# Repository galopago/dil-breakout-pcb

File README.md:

# BREAKOUT BOARDS FOR RF MODULES

Open source breakout boards for "stamp like" rf modules. Good for experimenting on a breadboard or to be used as sub-boards.

Read this in other languages: [Español](/assets/markdown/README.es.md)

Main features:

* Every pin is accessible
* Compatible with solderless breadboard
* Double row header for maximizing free space on prototype boards

Breadboard                              | Space saver right angle                    | Space saver rised                           
----------------------------------------|--------------------------------------------|---------------------------------------------
 |  | 

## Versions

There are several board versions, each one with different personalities

| HINT     | CHIP                  | LINK                                     
|----------|-----------------------|--------------------------------------
| RAK3172  | STM32WLE5CC           | [RAK3172](/rak3172)  
| RAK11300 | RP2040+SX1262         | [RAK11300](/rak11300)  
| SA818    | RENESAS MCU ?+RDA1846 | [SA818](/sa818)
| MS88SF2  | nRF52840              | [MS88SF2](/ms88sf2)

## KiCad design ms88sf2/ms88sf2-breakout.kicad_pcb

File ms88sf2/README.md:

# BREAKOUT BOARD FOR MS88SF2 MODULE

This board allows [Minew MS88SF2 modules](assets/pdf/MS88SF2elp
e.pdf) to be used on breadboard for prototyping. Open source and manufacturing files available. The main features are:

* Every pin is accessible
* Compatible with solderless breadboard
* Double row header for maximizing free space on prototype boards

## How to use this repository

The PCB was developed in KiCad V5.1,

## Directory structure

* The root folder contains template KiCad files: project, schematic and PCB 
* /library folder contains additional symbols needed to edit printed schematic
* /modules folder contains additional footprints needed to edit printed circuit board
* /gerber folder contains ready to manufacture files.
* /assets folder contains support files for reade.md

## PINOUT

## BREADBOARD

Pitch compatible with solderless breadboard

## DOUBLE ROW RIGHT ANGLE

Space saver option when enclosure's height allows it

 FRONT                             | SIDE                             | UPPER                            
-----------------------------------|----------------------------------|-----------------------------------
||

## DOUBLE ROW RISED

Space saver option for batteries or additional electronics. Uses long pin headers with spacers to reach the maximun allowable height

 SIDE                              | RISED                          
-----------------------------------|--------------------------------
|

## PCB

 SINGLE                            | PANEL                          
-----------------------------------|--------------------------------
|

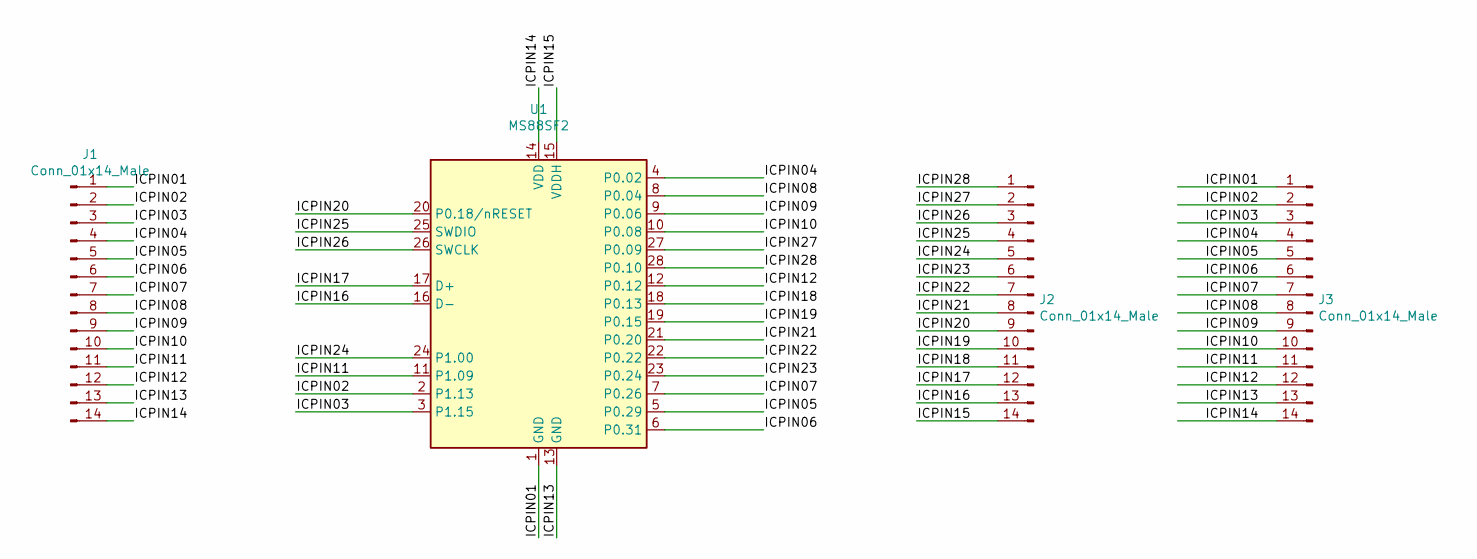
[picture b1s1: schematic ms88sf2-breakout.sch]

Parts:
J1, J2, J3: Conn_01x14_Male; PinHeader_1x14_P2.54mm_Vertical
U1: MS88SF2

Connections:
/ICPIN01: J1.1, J3.1, U1.1 (GND)
/ICPIN02: J1.2, J3.2, U1.2 (P1.13)
/ICPIN03: J1.3, J3.3, U1.3 (P1.15)
/ICPIN04: J1.4, J3.4, U1.4 (P0.02)
/ICPIN05: J1.5, J3.5, U1.5 (P0.29)
/ICPIN06: J1.6, J3.6, U1.6 (P0.31)
/ICPIN07: J1.7, J3.7, U1.7 (P0.26)
/ICPIN08: J1.8, J3.8, U1.8 (P0.04)
/ICPIN09: J1.9, J3.9, U1.9 (P0.06)
/ICPIN10: J1.10, J3.10, U1.10 (P0.08)
/ICPIN11: J1.11, J3.11, U1.11 (P1.09)
/ICPIN12: J1.12, J3.12, U1.12 (P0.12)
/ICPIN13: J1.13, J3.13, U1.13 (GND)
/ICPIN14: J1.14, J3.14, U1.14 (VDD)
/ICPIN15: J2.14, U1.15 (VDDH)
/ICPIN16: J2.13, U1.16 (D-)
/ICPIN17: J2.12, U1.17 (D+)
/ICPIN18: J2.11, U1.18 (P0.13)
/ICPIN19: J2.10, U1.19 (P0.15)
/ICPIN20: J2.9, U1.20 (P0.18/nRESET)
/ICPIN21: J2.8, U1.21 (P0.20)
/ICPIN22: J2.7, U1.22 (P0.22)
/ICPIN23: J2.6, U1.23 (P0.24)
/ICPIN24: J2.5, U1.24 (P1.00)
/ICPIN25: J2.4, U1.25 (SWDIO)
/ICPIN26: J2.3, U1.26 (SWCLK)
/ICPIN27: J2.2, U1.27 (P0.09)
/ICPIN28: J2.1, U1.28 (P0.10)

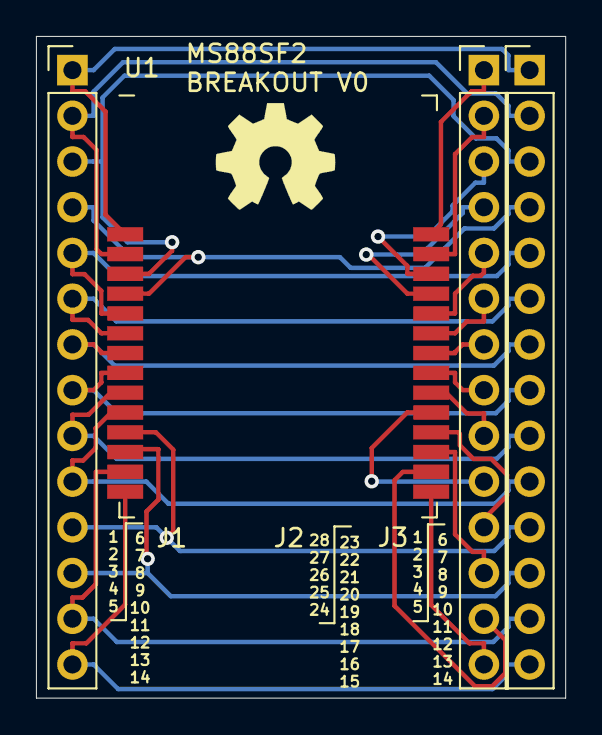
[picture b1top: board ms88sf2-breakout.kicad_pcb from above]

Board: 2 copper layers, 29.4 x 36.8 mm, 4 parts (0 on the bottom side), 28 nets.

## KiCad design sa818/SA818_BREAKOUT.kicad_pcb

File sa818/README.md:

# BREAKOUT BOARD FOR SA818 MODULE

This board allows [NiceRF SA818 modules](assets/pdf/SA818.pdf) to be used on breadboard for prototyping. Open source and manufacturing files available. The main features are:

* Every pin is accessible
* Compatible with solderless breadboard
* Double row header for maximizing free space on prototype boards
* Pads for U.Fl RF connector
* Pads for custom output pi filter

## How to use this repository

The PCB was developed in KiCad V5.1,

## Directory structure

* The root folder contains template KiCad files: project, schematic and PCB 
* /library folder contains additional symbols needed to edit printed schematic
* /modules folder contains additional footprints needed to edit printed circuit board
* /gerber folder contains ready to manufacture files.
* /assets folder contains support files for reade.md

## PINOUT

## BREADBOARD

Pitch compatible with solderless breadboard

## DOUBLE ROW RIGHT ANGLE

Space saver option when enclosure's height allows it

 FRONT                             | SIDE                             | UPPER                            
-----------------------------------|----------------------------------|-----------------------------------
||

## DOUBLE ROW RISED

Space saver option for batteries or additional electronics. Uses long pin headers with spacers to reach the maximun allowable height

 SIDE                              | RISED                          
-----------------------------------|--------------------------------
|

## PCB

 SINGLE                            | PANEL                          
-----------------------------------|--------------------------------
|

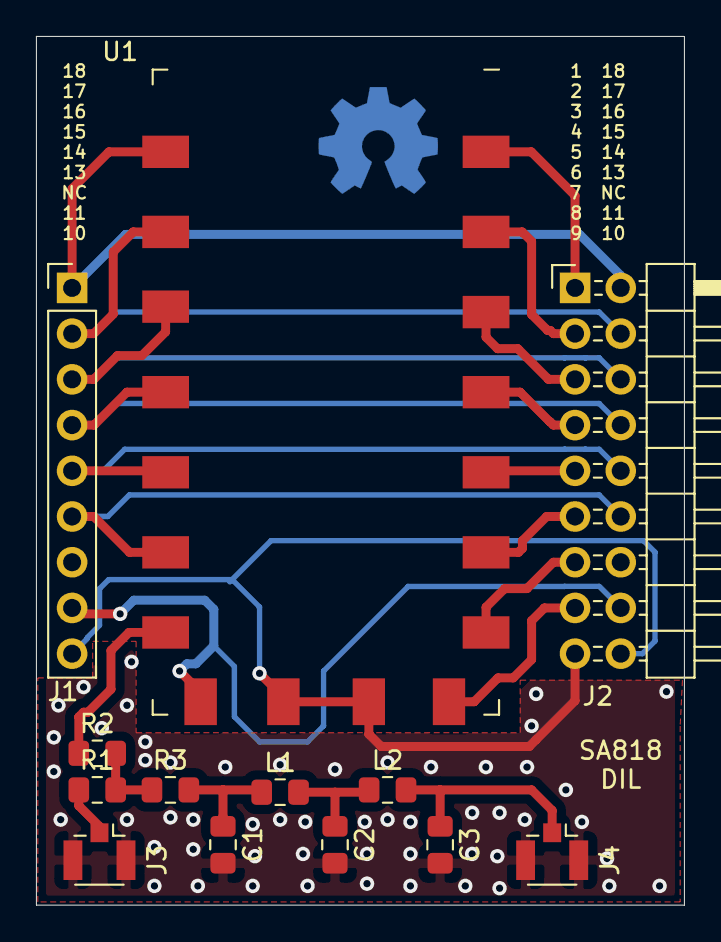
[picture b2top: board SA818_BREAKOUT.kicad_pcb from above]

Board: 2 copper layers, 36.0 x 48.3 mm, 13 parts (0 on the bottom side), 22 nets.

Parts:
C1, C2, C3: C; C_0805_2012Metric_Pad1.15x1.40mm_HandSolder
J1: Conn_01x09_Male; PinHeader_1x09_P2.54mm_Vertical
J2: Conn_02x09_Odd_Even; PinHeader_2x09_P2.54mm_Horizontal
J3, J4: Conn_Coaxial; U.FL_Hirose_U.FL-R-SMT-1_Vertical
L1, L2: L; L_0805_2012Metric_Pad1.15x1.40mm_HandSolder
R1, R2, R3: R; R_0805_2012Metric_Pad1.15x1.40mm_HandSolder
U1: SA818

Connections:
unnamed: C1.1, L1.1, R3.2
unnamed: C1.2, C2.2, C3.2, J1.9, J2.17, J2.18, J3.2, J4.2, U1.9, U1.10
unnamed: C2.1, L1.2, L2.1
unnamed: C3.1, J4.1, L2.2
unnamed: J1.1, J2.2, U1.18
unnamed: J1.2, J2.4, U1.17
unnamed: J1.3, J2.6, U1.16
unnamed: J1.4, J2.8, U1.15
unnamed: J1.5, J2.10, U1.14
unnamed: J1.6, J2.12, U1.13
unnamed: J1.8, J2.16, U1.11
unnamed: J2.1, U1.1
unnamed: J2.3, U1.2
unnamed: J2.5, U1.3
unnamed: J2.7, U1.4
unnamed: J2.9, U1.5
unnamed: J2.11, U1.6
unnamed: J2.13, U1.7
unnamed: J2.15, U1.8
unnamed: J3.1, R1.1
unnamed: R1.2, R2.2, R3.1
unnamed: R2.1, U1.12

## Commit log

2022-03-01 starting project RAK3712
2022-03-01 started RAK3172 symbol
2022-03-01 sch:(DIL_BREAKOUT_PCB RAK 3712)changing pins
2022-03-02 sch:(DIL_BREAKOUT_PCB RAK 3712)pins arranged
2022-03-02 sch:(DIL_BREAKOUT_PCB RAK 3712)shrinked
2022-03-02 sch:(DIL_BREAKOUT_PCB RAK 3712)tied to headers
2022-03-02 foot:(DIL_BREAKOUT_PCB RAK 3712)started foot
2022-03-02 foot:(DIL_BREAKOUT_PCB RAK 3712)finished foot
2022-03-02 foot:(DIL_BREAKOUT_PCB RAK 3712)ready for route
2022-03-02 foot:(DIL_BREAKOUT_PCB RAK 3712)first route
2022-03-02 pcb:(DIL_BREAKOUT_PCB RAK 3712)routed!
2022-03-02 pcb-sch:(DIL_BREAKOUT_PCB RAK 3712)changed name!
2022-03-02 proj:(DIL_BREAKOUT_PCB RAK 3712)changed project filenames
2022-03-02 proj:(DIL_BREAKOUT_PCB RAK 3712)updated ic tags
2022-03-02 pcb:(DIL_BREAKOUT_PCB RAK 3172) minor adjustments
2022-03-02 pcb:(DIL_BREAKOUT_PCB RAK 3172) silks headers
2022-03-02 pcb:(DIL_BREAKOUT_PCB RAK 3172)single gerber
2022-03-02 pcb:(DIL_BREAKOUT_PCB RAK 3172)panel gerber
2022-03-02 pcb:(DIL_BREAKOUT_PCB RAK 11300)expanded and routed
2022-03-03 pcb:(DIL_BREAKOUT_PCB RAK 11300)single gerber
2022-03-03 pcb:(DIL_BREAKOUT_PCB RAK 11300)panel gerber
2022-03-03 proj:(DIL_BREAKOUT_PCB SA 818)migrated project
2022-04-09 doc:(dil-breakout)renamed folders
2022-04-09 doc:(dil-breakout rak3172)started readme
2022-04-09 doc:(dil-breakout rak3172)pinout svg started
2022-04-09 doc:(dil-breakout rak3172)pinout svg finished
2022-04-09 doc:(dil-breakout rak3172)updated pic
2022-04-09 doc:(dil-breakout rak3172)readme updated
2022-04-09 doc:(dil-breakout rak3172)readme right angle
2022-04-09 doc:(dil-breakout rak3172)readme right angle+
2022-04-09 doc:(dil-breakout rak3172)readme pcb
2022-04-10 doc:(dil-breakout rak3172)readme spell cheked
2022-04-10 doc:(dil-breakout rak11300)readme started
2022-04-10 doc:(dil-breakout rak11300)readme started typo
2022-04-10 doc:(dil-breakout sa818)readme started
2022-04-10 doc:(dil-breakout rak11300)pinout
2022-04-10 doc:(dil-breakout sa818)pinout
2022-04-10 doc:(dil-breakout sa818)deleted tmp files
2022-04-10 doc:(dil-breakout rak11300)pics
2022-04-10 doc:(dil-breakout rak11300)all pics
2022-04-10 doc:(dil-breakout sa810)some pics
2022-04-10 doc:(dil-breakout sa810)pcb pics
2022-04-10 doc:(dil-breakout sa810)double row pics
2022-04-12 doc:(dil-breakout root)started EN readme
2022-04-12 doc:(dil-breakout root)started EN readme fix
2022-04-12 doc:(dil-breakout root)started SP readme
2022-04-12 doc:(dil-breakout root)started SP readme+
2022-04-12 doc:(dil-breakout root)started SP readme++
2022-04-12 doc:(dil-breakout root)started SP readme+++
2022-04-12 doc:(dil-breakout root)LICENSE
2022-08-21 started MS88SF2
2022-08-21 MS88SF2 routed
2022-08-21 single gerber
2022-09-19 changed MS88SF2 pic
2022-09-19 changed MS88SF2 pic+
2022-09-19 changed MS88SF2 pic++
2022-09-19 changed MS88SF2 pic+++
2022-09-19 changed MS88SF2 pic++++
2022-09-19 changed MS88SF2 pic+++++
2022-09-19 deleted old MS88SF2 pic
2022-09-19 deleted old MS88SF2 pic+
2022-09-19 master readme
2022-09-19 master readme pic
